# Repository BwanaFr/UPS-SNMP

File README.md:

# USB UPS to SNMP

## Introduction

This small device is attended to publish USB UPS (tested on some APC models) values to SNMP (v2c).

## Building

### Hardware
Hardware design files (PCB and 3D enclosure) is stored in the `hardware` folder.

### Firmware
The ESP32S3 firmware is built with PlatformIO.
Releases of the firmware are available on my GitHub page.

#### Configuration names
Some configurations are supported.

## Usage
Connect an USB cable in the USB A connector, a PoE enabled RJ45 ethernet connection.
The device is starting using a default IP of 10.10.11.200.
Please navigate to http://10.10.11.200 to change settings (your PC needs to be on the same network).

### Reset to default using buttons procedure
You can do a "on site" reset using the navigation button. To do so, please use this procedure.

1. Connect ethernet cable
2. You have one second to push the button
3. The LED will go white
4. Relase the button
5. Within 200ms, press again the buton
6. Device will start with default configuration

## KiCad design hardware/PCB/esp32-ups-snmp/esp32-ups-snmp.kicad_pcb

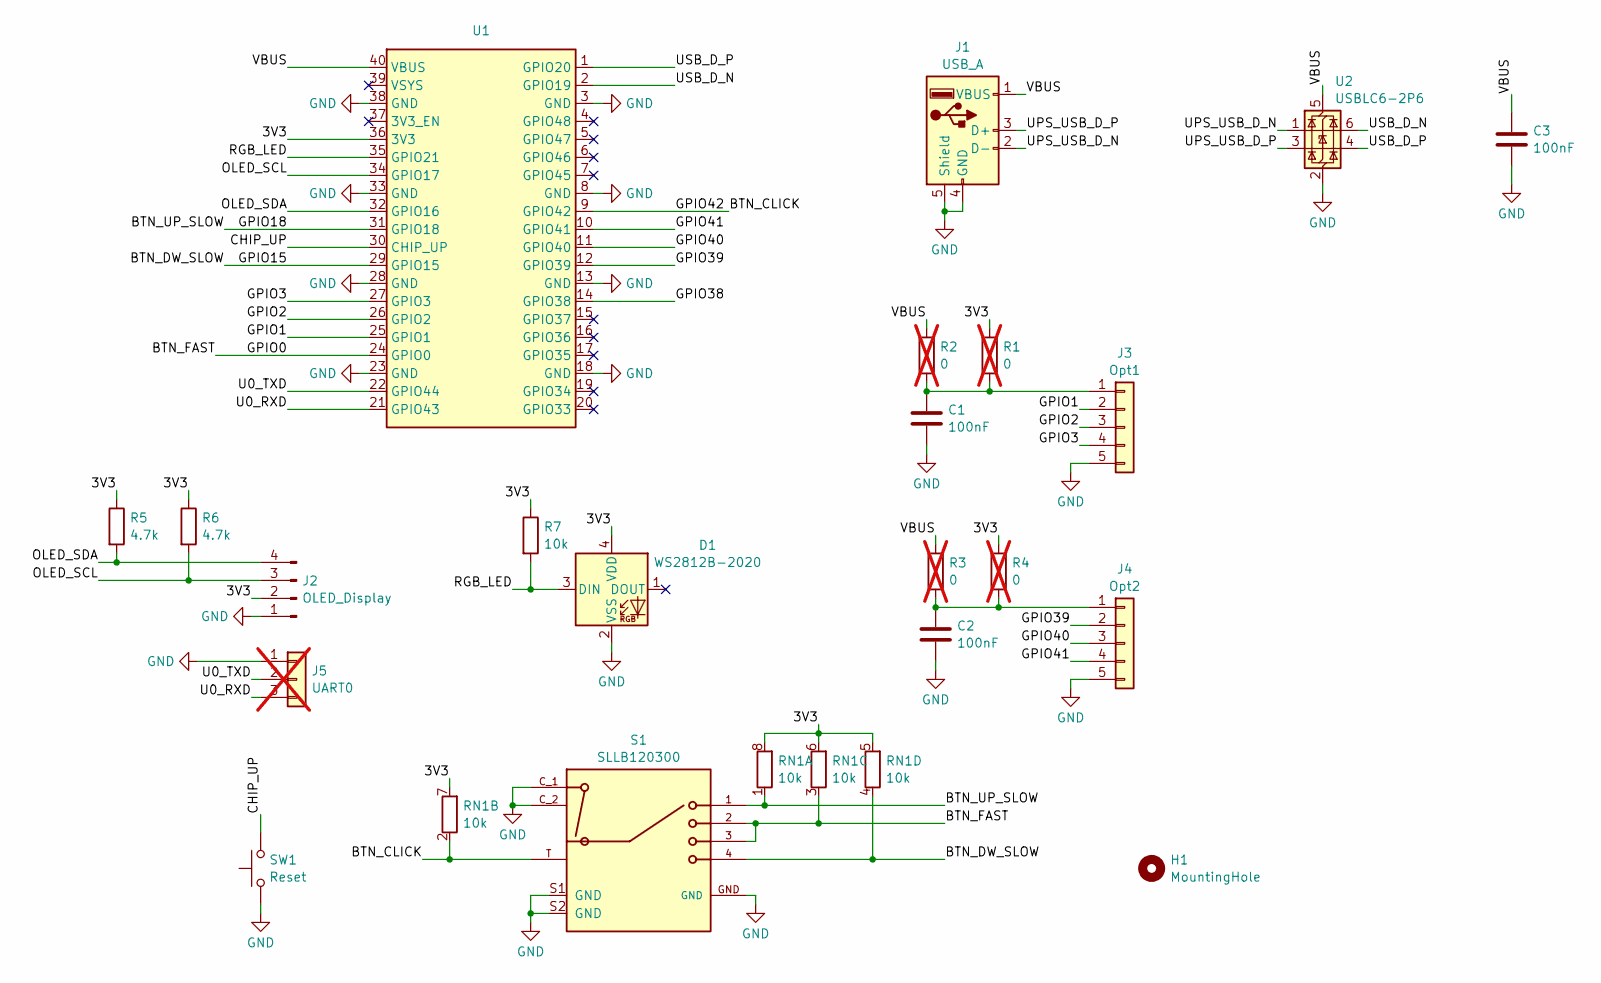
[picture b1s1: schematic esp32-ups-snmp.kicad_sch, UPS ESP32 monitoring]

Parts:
C1, C2, C3: 100nF; C_0603_1608Metric
D1: WS2812B-2020; LED_WS2812B-2020_PLCC4_2.0x2.0mm; LCSC C965555
H1: MountingHole; MountingHole_2.2mm_M2_DIN965
J1: USB_A; USB_A_Wuerth_614004134726_Horizontal
J2: OLED_Display; PinSocket_1x04_P2.54mm_Vertical
J3: Opt1; JST_ZE_S05B-ZESK-2D_1x05_P1.50mm_Horizontal
J4: Opt2; JST_ZE_S05B-ZESK-2D_1x05_P1.50mm_Horizontal
J5: UART0; PinHeader_1x03_P2.54mm_Vertical; not fitted
R1, R2, R3, R4: 0; R_0603_1608Metric; not fitted
R5, R6: 4.7k; R_0603_1608Metric
R7: 10k; R_0603_1608Metric
RN1: 10k; R_Array_Convex_4x0603; LCSC C29718
S1: SLLB120300; SW_SLLB120300; LCSC C255512
SW1: Reset; SW_SPST_B3U-3000P
U1: waveshare_esp32-s3_eth
U2: USBLC6-2P6; SOT-666

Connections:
/3V3: D1.4 (VDD), J2.2, R1.2, R4.2, R5.1, R6.1, R7.1, RN1.5 (R4.2), RN1.6 (R3.2), RN1.7 (R2.2), RN1.8 (R1.2), U1.36 (3V3)
/BTN_CLICK: RN1.2 (R2.1), S1.T, U1.9 (GPIO42)
/BTN_DW_SLOW: RN1.4 (R4.1), S1.4, U1.29 (GPIO15)
/BTN_FAST: RN1.3 (R3.1), S1.2, S1.3, U1.24 (GPIO0)
/BTN_UP_SLOW: RN1.1 (R1.1), S1.1, U1.31 (GPIO18)
/CHIP_UP: SW1.2, U1.30 (CHIP_UP)
/GPIO1: J3.2, U1.25 (GPIO1)
/GPIO2: J3.3, U1.26 (GPIO2)
/GPIO3: J3.4, U1.27 (GPIO3)
/GPIO38: U1.14 (GPIO38)
/GPIO39: J4.2, U1.12 (GPIO39)
/GPIO40: J4.3, U1.11 (GPIO40)
/GPIO41: J4.4, U1.10 (GPIO41)
/OLED_SCL: J2.3, R6.2, U1.34 (GPIO17)
/OLED_SDA: J2.4, R5.2, U1.32 (GPIO16)
/RGB_LED: D1.3 (DIN), R7.2, U1.35 (GPIO21)
/U0_RXD: J5.3, U1.21 (GPIO43)
/U0_TXD: J5.2, U1.22 (GPIO44)
/UPS_USB_D_N: J1.2 (D-), U2.1 (I/O1)
/UPS_USB_D_P: J1.3 (D+), U2.3 (I/O2)
/USB_D_N: U1.2 (GPIO19), U2.6 (I/O1)
/USB_D_P: U1.1 (GPIO20), U2.4 (I/O2)
/VBUS: C3.1, J1.1 (VBUS), R2.2, R3.2, U1.40 (VBUS), U2.5 (VBUS)
GND: C1.2, C2.2, C3.2, D1.2 (VSS), J1.4 (GND), J1.5 (Shield), J2.1, J3.5, J4.5, J5.1, S1.C_1, S1.C_2, S1.GND, S1.S1 (GND), S1.S2 (GND), SW1.1, U1.3 (GND), U1.8 (GND), U1.13 (GND), U1.18 (GND), U1.23 (GND), U1.28 (GND), U1.33 (GND), U1.38 (GND), U2.2 (GND)
unnamed: C1.1, J3.1, R1.1, R2.1
unnamed: C2.1, J4.1, R3.1, R4.1

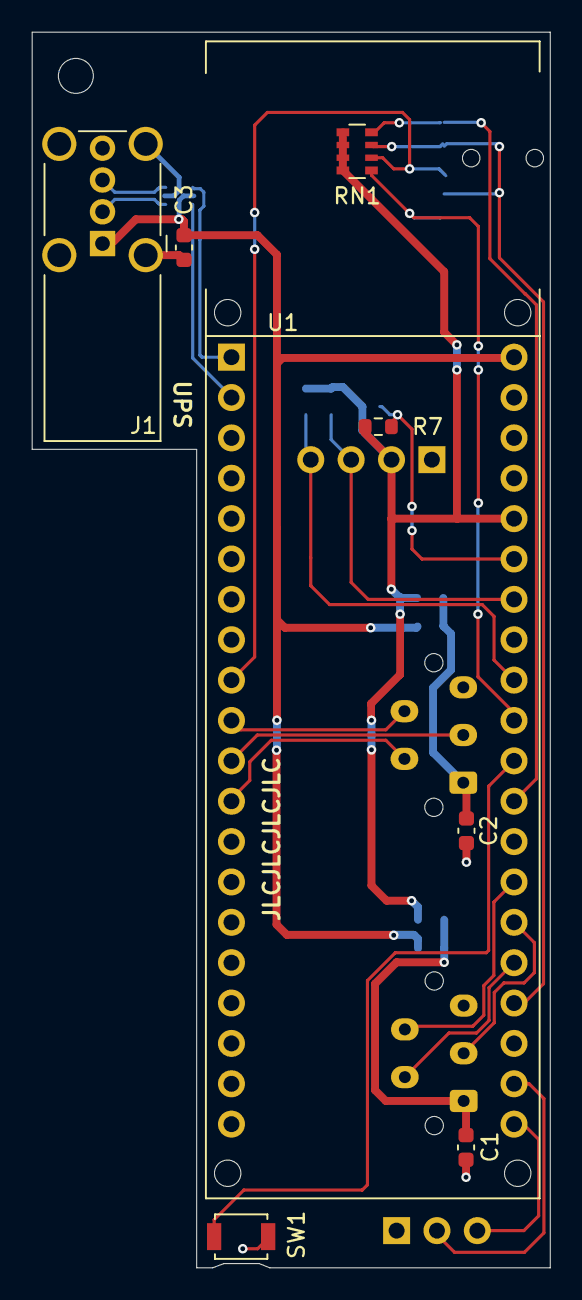
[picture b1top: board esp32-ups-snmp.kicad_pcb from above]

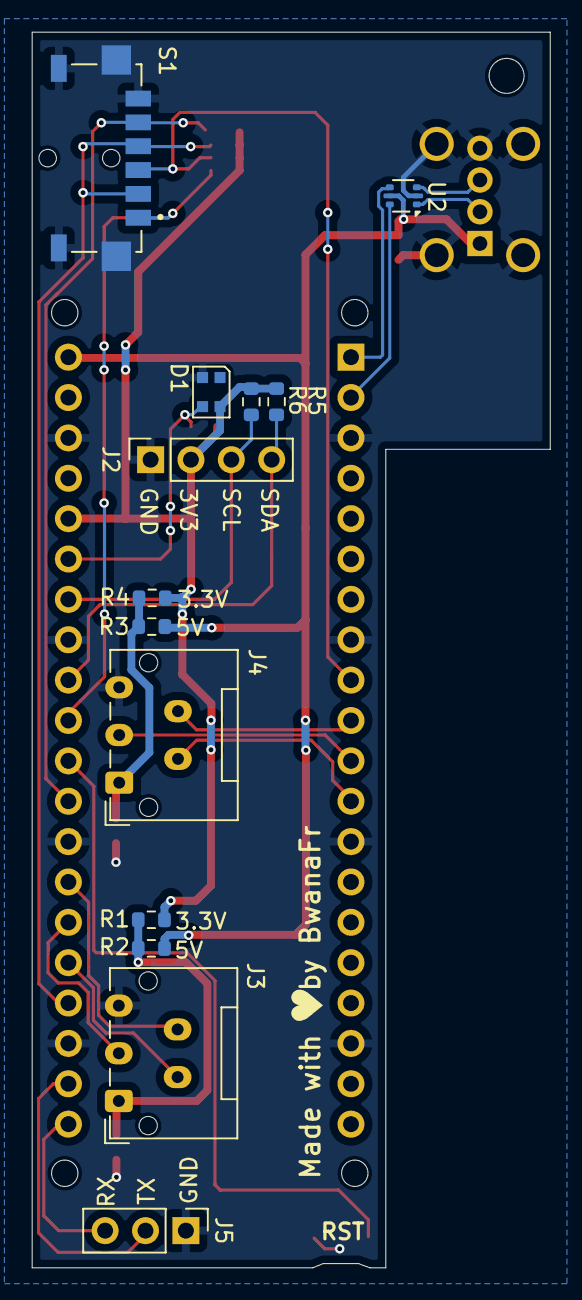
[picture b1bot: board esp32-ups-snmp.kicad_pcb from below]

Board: 2 copper layers, 32.6 x 77.8 mm, 22 parts (13 on the bottom side), 25 nets.

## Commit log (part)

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2026-03-25 First public commit
2026-03-25 Added small firmware to test hardware boards
2026-03-25 feat: Adding release on CI
2026-03-25 fix: Removed generated file from git
2026-06-01 Added SNMP bulk get support
2026-06-12 Fixed static IP at reset
2026-06-24 Refresh switch interfaces every 30s if not interfaces found
2026-06-24 Added switch status in webpage
2026-06-24 Added CPU temperature on webpage
2026-06-29 WIP on some Python tools
2026-06-29 WIP on flasher tool
2026-06-29 WIP on tools
2026-06-29 Fixed init when empty flash
